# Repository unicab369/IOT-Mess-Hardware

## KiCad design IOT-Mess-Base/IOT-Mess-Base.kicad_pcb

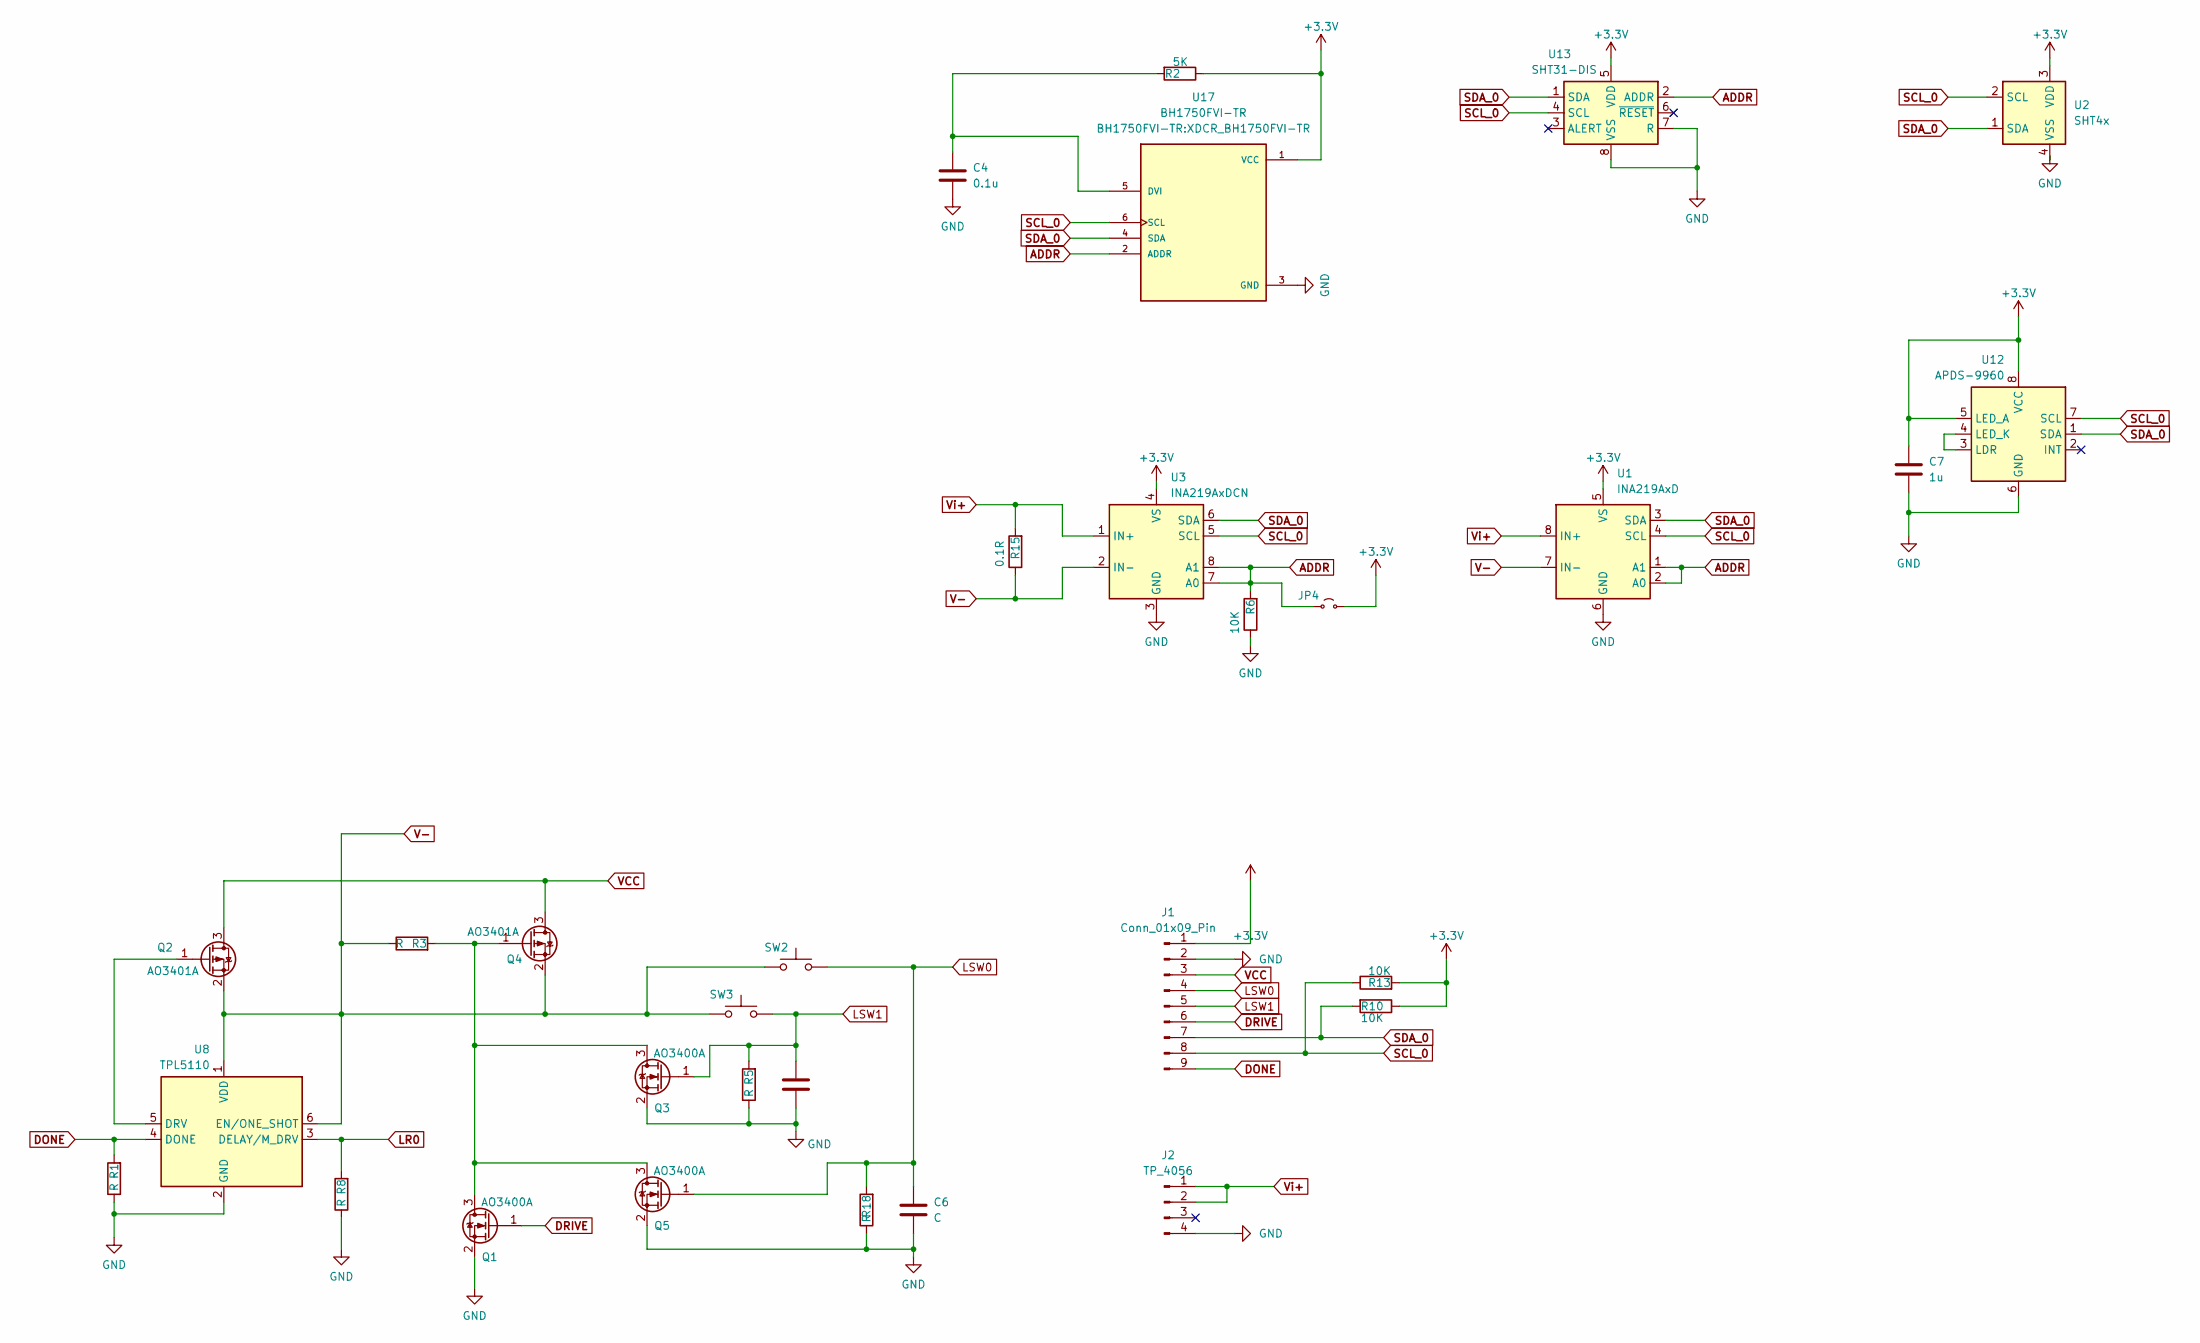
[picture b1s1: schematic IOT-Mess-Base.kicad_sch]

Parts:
C4: 0.1u; C_0603_1608Metric
C5, C6: C; C_0603_1608Metric
C7: 1u; C_0603_1608Metric
J1: Conn_01x09_Pin; PinHeader_1x09_P2.54mm_Vertical
J2: TP_4056; TP_Charger
JP4: Jp_2; SolderJumper-2_P1.3mm_Open_Pad1.0x1.5mm
Q1, Q3, Q5: AO3400A; SOT-23
Q2, Q4: AO3401A; SOT-23
R1, R3, R5, R8, R18: R; R_0603_1608Metric
R2: 5K; R_0603_1608Metric
R6, R10, R13: 10K; R_0603_1608Metric
R15: 0.1R; R_2512_6332Metric
SW2, SW3: SW_Push; SW_SPST_PTS810
U1: INA219AxD; SOIC-8_3.9x4.9mm_P1.27mm
U2: SHT4x; Sensirion_DFN-4_1.5x1.5mm_P0.8mm_SHT4x_NoCentralPad
U3: INA219AxDCN; SOT-23-8
U8: TPL5110; SOT-23-6
U12: APDS-9960; Avago_APDS-9960
U13: SHT31-DIS; Sensirion_DFN-8-1EP_2.5x2.5mm_P0.5mm_EP1.1x1.7mm
U17: BH1750FVI-TR; XDCR_BH1750FVI-TR; PARTREV D

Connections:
+3.3V: C7.1, J1.1, JP4.2 (B), R2.1, R10.1, R13.2, U1.5 (VS), U2.3 (VDD), U3.4 (VS), U12.5 (LED_A), U12.8 (VCC), U13.5 (VDD), U17.1 (VCC)
ADDR: JP4.1 (A), R6.2, U1.1 (A1), U1.2 (A0), U3.7 (A0), U3.8 (A1), U13.2 (ADDR), U17.2 (ADDR)
DONE: J1.9, R1.2, U8.4 (DONE)
DRIVE: J1.6, Q1.1 (G)
GND: C4.2, C5.2, C6.2, C7.2, J1.2, J2.4, Q1.2 (S), Q3.2 (S), Q5.2 (S), R1.1, R5.1, R6.1, R8.1, R18.1, U1.6 (GND), U2.4 (VSS), U3.3 (GND), U8.2 (GND), U12.6 (GND), U13.7 (R), U13.8 (VSS), U13.9 (VSS), U17.3 (GND)
LR0: R8.2, U8.3 (DELAY/M_DRV)
LSW0: C6.1, J1.4, Q5.1 (G), R18.2, SW2.2
LSW1: C5.1, J1.5, Q3.1 (G), R5.2, SW3.2
unnamed: Q1.3 (D), Q3.3 (D), Q4.1 (G), Q5.3 (D), R3.2
unnamed: Q2.1 (G), U8.5 (DRV)
unnamed: U12.3 (LDR), U12.4 (LED_K)
unnamed: C4.1, R2.2, U17.5 (DVI)
SCL_0: J1.8, R13.1, U1.4 (SCL), U2.2 (SCL), U3.5 (SCL), U12.7 (SCL), U13.4 (SCL), U17.6 (SCL)
SDA_0: J1.7, R10.2, U1.3 (SDA), U2.1 (SDA), U3.6 (SDA), U12.1 (SDA), U13.1 (SDA), U17.4 (SDA)
V-: Q2.2 (S), Q4.2 (S), R3.1, R15.1, SW2.1, SW3.1, U1.7 (IN-), U3.2 (IN-), U8.1 (VDD), U8.6 (EN/ONE_SHOT)
VCC: J1.3, Q2.3 (D), Q4.3 (D)
Vi+: J2.1, J2.2, R15.2, U1.8 (IN+), U3.1 (IN+)

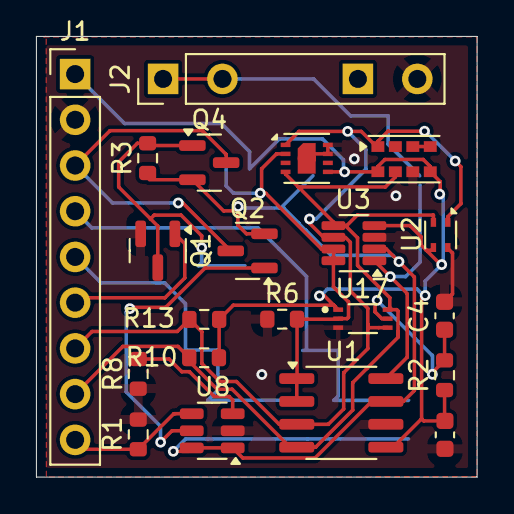
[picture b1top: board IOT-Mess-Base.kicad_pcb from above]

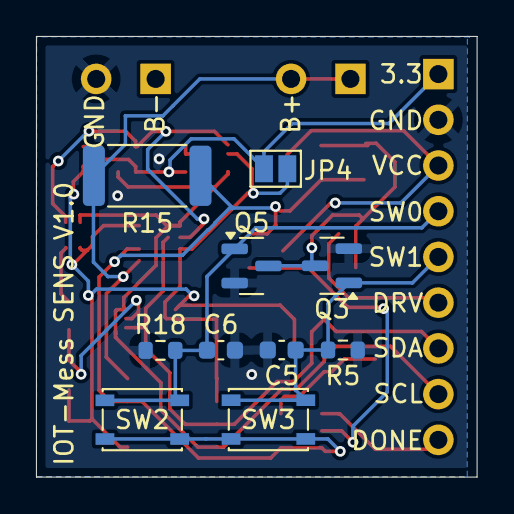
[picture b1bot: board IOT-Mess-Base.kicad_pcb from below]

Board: 2 copper layers, 24.5 x 24.5 mm, 31 parts (10 on the bottom side), 17 nets.

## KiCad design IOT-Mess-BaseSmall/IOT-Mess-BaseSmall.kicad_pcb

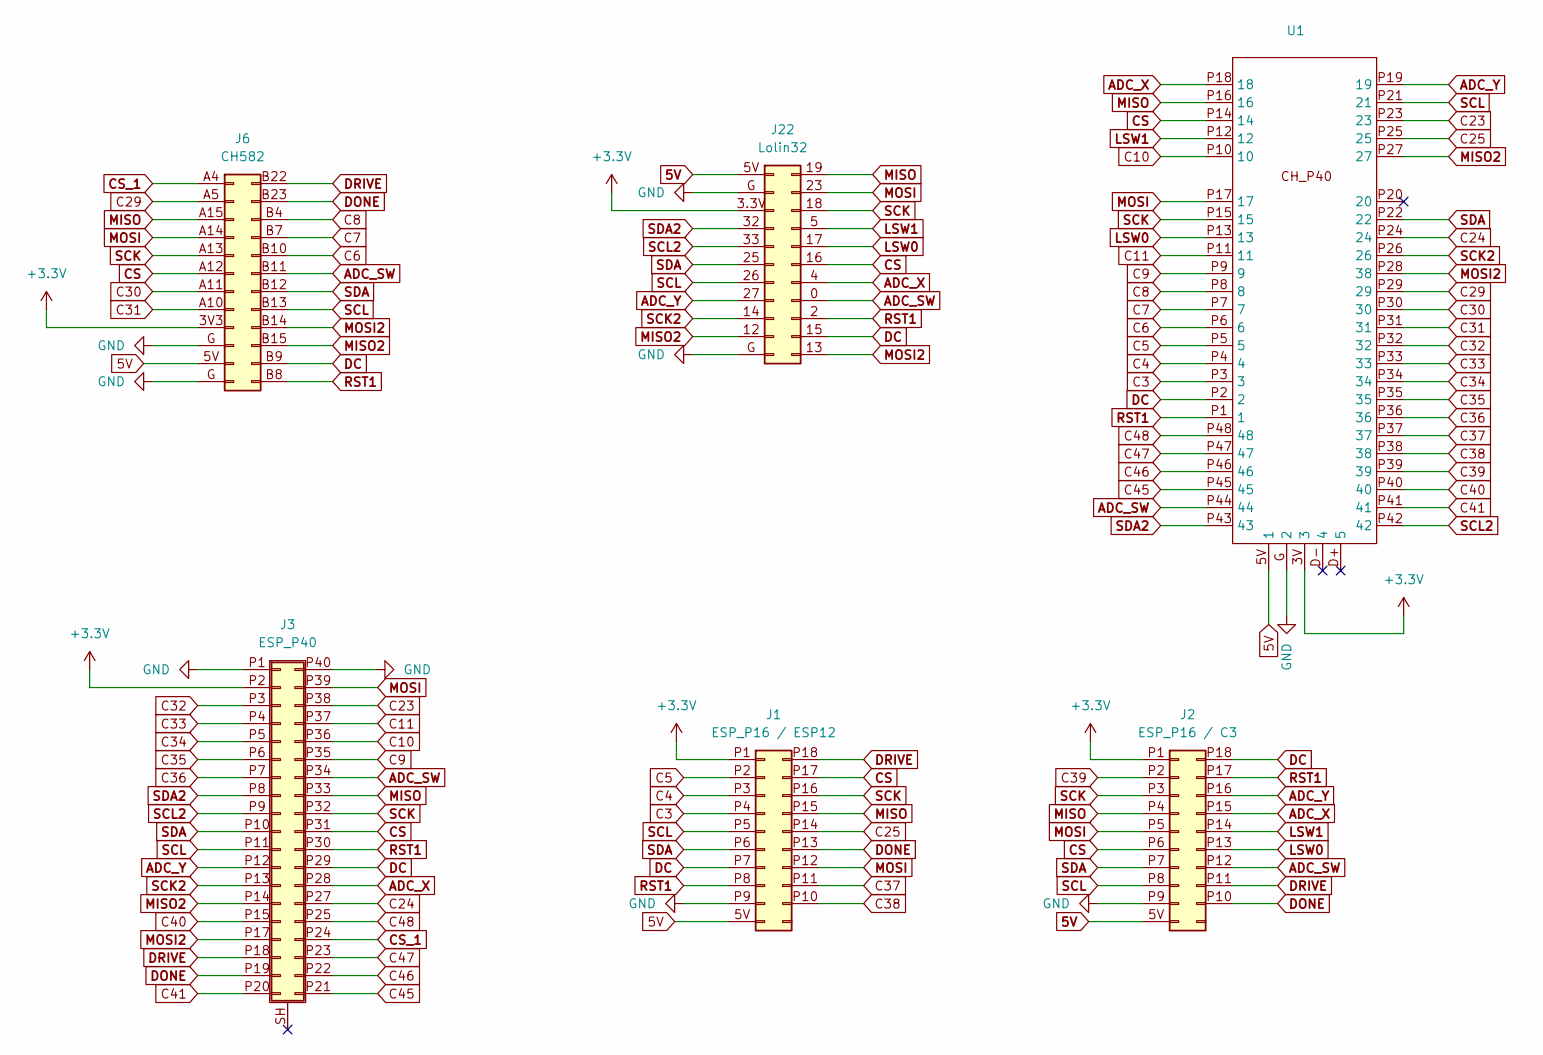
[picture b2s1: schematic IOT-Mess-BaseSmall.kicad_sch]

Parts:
J1: ESP_P16 / ESP12; ESP_P16
J2: ESP_P16 / C3; ESP_P16
J3: ESP_P40
J6: CH582; CH582_Base
J22: Lolin32; Lolin32-Adapter
U1: CH_P48

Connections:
5V: J1.5V (Pin_10), J2.5V (Pin_10), J6.5V (Pin_11), J22.5V (Pin_1), U1.5V (1)
+3.3V: J1.P1 (Pin_1), J2.P1 (Pin_1), J3.P2 (Pin_2), J6.3V3 (Pin_9), J22.3.3V (Pin_3), U1.3V (3)
ADC_SW: J2.P12 (Pin_14), J3.P34 (Pin_26), J6.B11 (Pin_18), J22.0 (Pin_19), U1.P44 (44)
ADC_X: J2.P15 (Pin_17), J3.P28 (Pin_32), J22.4 (Pin_18), U1.P18 (18)
ADC_Y: J2.P16 (Pin_18), J3.P12 (Pin_12), J22.27 (Pin_8), U1.P19 (19)
C3: J1.P4 (Pin_4), U1.P3 (3)
C4: J1.P3 (Pin_3), U1.P4 (4)
C5: J1.P2 (Pin_2), U1.P5 (5)
C6: J6.B10 (Pin_17), U1.P6 (6)
C7: J6.B7 (Pin_16), U1.P7 (7)
C8: J6.B4 (Pin_15), U1.P8 (8)
C9: J3.P35 (Pin_25), U1.P9 (9)
C10: J3.P36 (Pin_24), U1.P10 (10)
C11: J3.P37 (Pin_23), U1.P11 (11)
C23: J3.P38 (Pin_22), U1.P23 (23)
C24: J3.P27 (Pin_33), U1.P24 (24)
C25: J1.P14 (Pin_16), U1.P25 (25)
C29: J6.A5 (Pin_2), U1.P29 (29)
C30: J6.A11 (Pin_7), U1.P30 (30)
C31: J6.A10 (Pin_8), U1.P31 (31)
C32: J3.P3 (Pin_3), U1.P32 (32)
C33: J3.P4 (Pin_4), U1.P33 (33)
C34: J3.P5 (Pin_5), U1.P34 (34)
C35: J3.P6 (Pin_6), U1.P35 (35)
C36: J3.P7 (Pin_7), U1.P36 (36)
C37: J1.P11 (Pin_13), U1.P37 (37)
C38: J1.P10 (Pin_12), U1.P38 (38)
C39: J2.P2 (Pin_2), U1.P39 (39)
C40: J3.P15 (Pin_15), U1.P40 (40)
C41: J3.P20 (Pin_19), U1.P41 (41)
C45: J3.P21 (Pin_38), U1.P45 (45)
C46: J3.P22 (Pin_37), U1.P46 (46)
C47: J3.P23 (Pin_36), U1.P47 (47)
C48: J3.P25 (Pin_34), U1.P48 (48)
CS: J1.P17 (Pin_19), J2.P6 (Pin_6), J3.P31 (Pin_29), J6.A12 (Pin_6), J22.16 (Pin_17), U1.P14 (14)
CS_1: J3.P24 (Pin_35), J6.A4 (Pin_1)
DC: J1.P7 (Pin_7), J2.P18 (Pin_20), J3.P29 (Pin_31), J6.B9 (Pin_23), J22.15 (Pin_21), U1.P2 (2)
DONE: J1.P13 (Pin_15), J2.P10 (Pin_12), J3.P19 (Pin_18), J6.B23 (Pin_14)
DRIVE: J1.P18 (Pin_20), J2.P11 (Pin_13), J3.P18 (Pin_17), J6.B22 (Pin_13)
GND: J1.P9 (Pin_9), J2.P9 (Pin_9), J3.P1 (Pin_1), J3.P40 (Pin_20), J6.G (Pin_10), J22.G (Pin_2), U1.G (2)
LSW0: J2.P13 (Pin_15), J22.17 (Pin_16), U1.P13 (13)
LSW1: J2.P14 (Pin_16), J22.5 (Pin_15), U1.P12 (12)
MISO: J1.P15 (Pin_17), J2.P4 (Pin_4), J3.P33 (Pin_27), J6.A15 (Pin_3), J22.19 (Pin_12), U1.P16 (16)
MISO2: J3.P14 (Pin_14), J6.B15 (Pin_22), J22.12 (Pin_10), U1.P27 (27)
MOSI: J1.P12 (Pin_14), J2.P5 (Pin_5), J3.P39 (Pin_21), J6.A14 (Pin_4), J22.23 (Pin_13), U1.P17 (17)
MOSI2: J3.P17 (Pin_16), J6.B14 (Pin_21), J22.13 (Pin_22), U1.P28 (38)
RST1: J1.P8 (Pin_8), J2.P17 (Pin_19), J3.P30 (Pin_30), J6.B8 (Pin_24), J22.2 (Pin_20), U1.P1 (1)
SCK: J1.P16 (Pin_18), J2.P3 (Pin_3), J3.P32 (Pin_28), J6.A13 (Pin_5), J22.18 (Pin_14), U1.P15 (15)
SCK2: J3.P13 (Pin_13), J22.14 (Pin_9), U1.P26 (26)
SCL: J1.P5 (Pin_5), J2.P8 (Pin_8), J3.P11 (Pin_11), J6.B13 (Pin_20), J22.26 (Pin_7), U1.P21 (21)
SCL2: J3.P9 (Pin_9), J22.33 (Pin_5), U1.P42 (42)
SDA: J1.P6 (Pin_6), J2.P7 (Pin_7), J3.P10 (Pin_10), J6.B12 (Pin_19), J22.25 (Pin_6), U1.P22 (22)
SDA2: J3.P8 (Pin_8), J22.32 (Pin_4), U1.P43 (43)

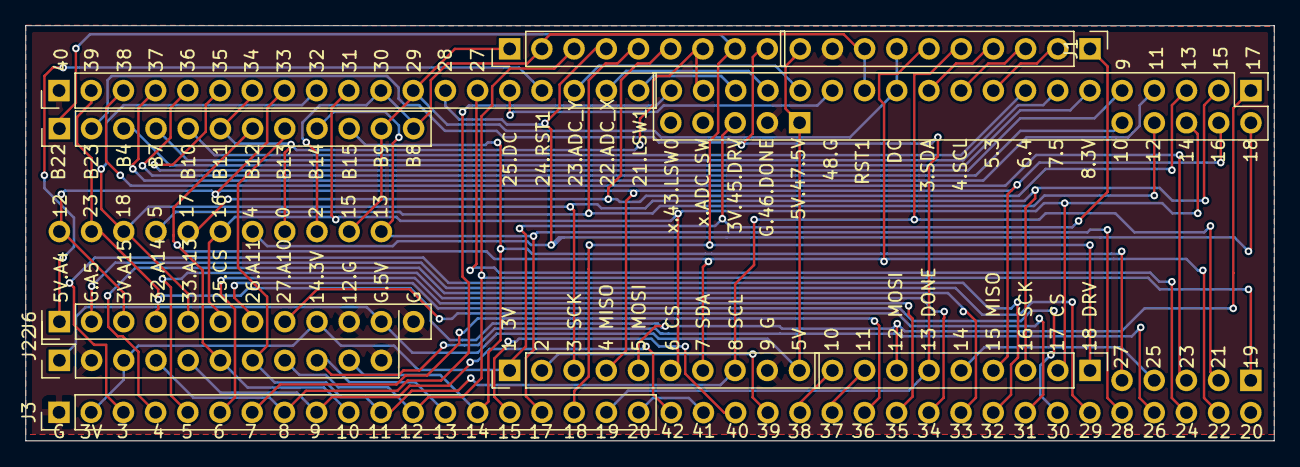
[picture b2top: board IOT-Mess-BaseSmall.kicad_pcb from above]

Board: 2 copper layers, 98.5 x 32.8 mm, 6 parts (0 on the bottom side), 53 nets.

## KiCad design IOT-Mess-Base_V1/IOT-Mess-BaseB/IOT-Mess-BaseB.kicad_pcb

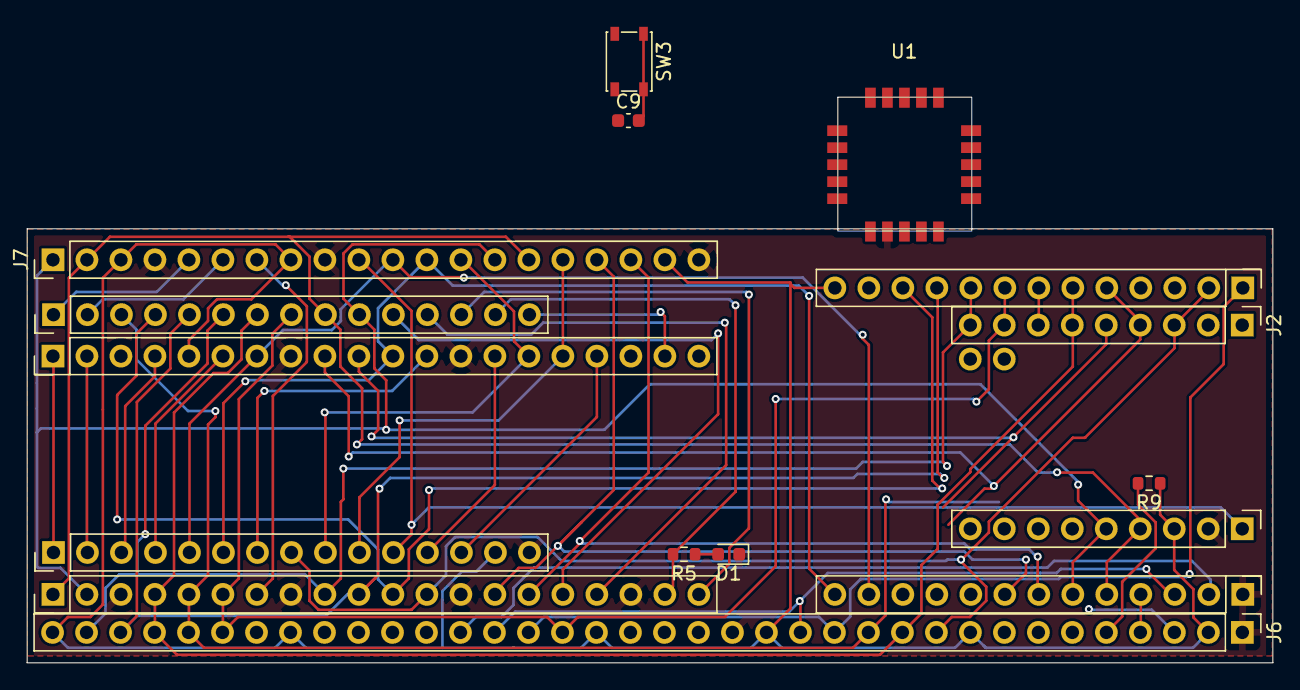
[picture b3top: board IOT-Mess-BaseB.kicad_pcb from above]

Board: 2 copper layers, 93.1 x 42.3 mm, 12 parts (0 on the bottom side), 40 nets.

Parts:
C9: .1u; C_0603_1608Metric
D1: LED; LED_0603_1608Metric
J1: Milk-V Duo
J2: SuperMini_ESP32-H2; SuperMiniH2
J3: CH_P20
J4: Lolin32-Lite
J6: Conn_01x36_Pin; PinHeader_1x36_P2.54mm_Vertical
J7: Conn_01x20_Pin; PinHeader_1x20_P2.54mm_Vertical
R5: 100R; R_0603_1608Metric
R9: 10K; R_0603_1608Metric
SW3: SW_Push; SW_SPST_PTS810
U1: E220-900

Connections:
5V: J2.5V (Pin_18), J3.5V (Pin_11), J7.10
+3.3V: J1.3V (Pin_36), J2.3V (Pin_16), J3.3V (Pin_14), J4.3V (Pin_13a), J6.2, J6.9, J6.15, J6.20, J6.29, J6.36, J7.3, J7.8, J7.19, R9.1, U1.1 (VCC)
ADC_SW: J6.5, R9.2
ADC_X: J1.32, J2.1 (Pin_4), J4.4 (Pin_5a), J6.3
ADC_Y: J1.31, J2.2 (Pin_5), J4.27 (Pin_4b), J6.4
CS_0: J1.6, J2.5 (Pin_8), J3.P13 (Pin_23), J4.5 (Pin_8a), J6.21, J6.31
CS_1: J1.12, J2.0 (Pin_3), J3.P8 (Pin_8), J4.15 (Pin_2a), J6.10
DC: J1.4, J2.3 (Pin_6), J3.P14 (Pin_22), J4.16 (Pin_6a), J6.11, J6.33
DONE: J1.25, J3.P10 (Pin_10), J7.16
DRIVE: J1.26, J3.P9 (Pin_9), J7.13
GND: C9.1, D1.1 (K), J1.G (Pin_3), J2.G (Pin_17), J3.G (Pin_15), J4.G (Pin_1b), J6.1, J6.16, J6.25, J6.30, J7.4, J7.9, J7.20, SW3.2, U1.2 (GND)
L5: J3.P20 (Pin_16), J7.5
L6: J3.P19 (Pin_17), J7.6
L7: J1.7, J7.7
LSW0: J1.34, J3.P5 (Pin_5), J4.36* (Pin_12b), J7.11
LSW1: J1.RUN (Pin_30), J3.P6 (Pin_6), J4.39* (Pin_13b), J7.12
M16: J1.16, J3.RST (Pin_26)
M17: J1.17, J3.XI (Pin_27)
M19: J1.19, J3.D- (Pin_29), R5.2
M20: C9.2, J1.20, J3.XO (Pin_28), SW3.1
M22: J1.22, J3.D+ (Pin_30)
M24: J1.24, J3.CC2 (Pin_13)
M27: J1.27, J3.CC1 (Pin_12)
M29: J1.29, J3.P7 (Pin_7)
M35: J1.35, J3.P4 (Pin_4)
M37: J1.EN (Pin_37), J3.P3 (Pin_3)
M39: J1.VSYS (Pin_39), J3.P2 (Pin_2)
M40: J1.VBUS (Pin_40), J3.P1 (Pin_1)
MISO_0: J1.11, J3.P17 (Pin_19), J4.19 (Pin_11a)
MISO_1: J4.12 (Pin_2b), J6.24
MOSI_0: J1.10, J3.P16 (Pin_20), J4.23 (Pin_10a), J6.34
MOSI_1: J4.13 (Pin_1a), J6.13, J6.22
unnamed: D1.2 (A), R5.1
RST1: J1.5, J2.4 (Pin_7), J3.P18 (Pin_18), J4.17 (Pin_7a), J6.12, J6.32, U1.3 (RST)
SCK_0: J1.9, J2.8 (Pin_9), J3.P15 (Pin_21), J4.18 (Pin_9a), J6.35
SCK_1: J4.14 (Pin_3b), J6.14, J6.23
SCL_0: J1.1, J2.14 (Pin_15), J3.P12 (Pin_24), J4.26 (Pin_5b), J7.2, J7.15
SCL_1: J1.15, J4.33 (Pin_7b), J7.18
SDA_0: J1.2, J2.13 (Pin_14), J3.P11 (Pin_25), J4.25 (Pin_6b), J7.1, J7.14
SDA_1: J1.14, J4.32 (Pin_8b), J7.17

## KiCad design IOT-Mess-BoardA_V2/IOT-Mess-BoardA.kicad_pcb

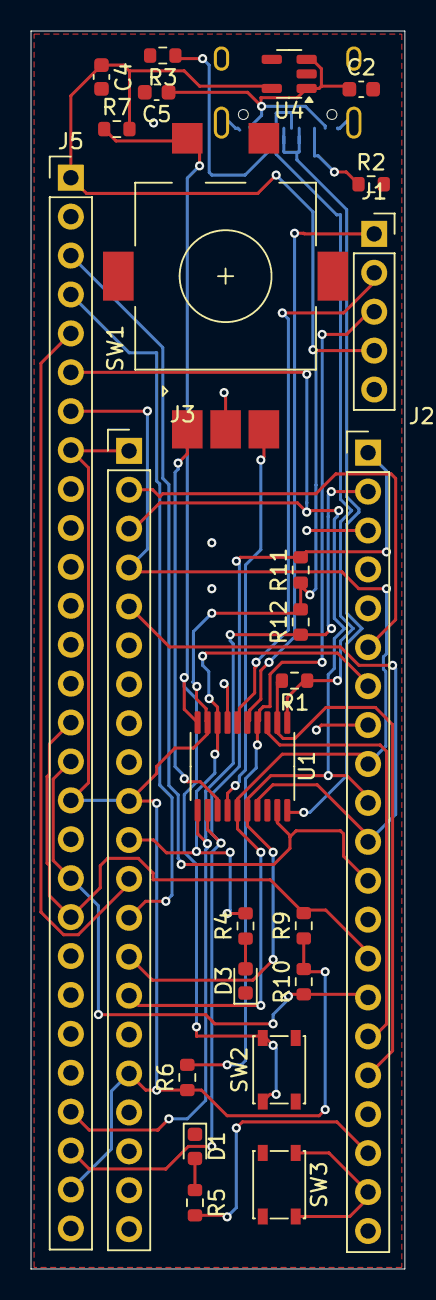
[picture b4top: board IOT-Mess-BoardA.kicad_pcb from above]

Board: 2 copper layers, 24.4 x 80.8 mm, 26 parts (1 on the bottom side), 32 nets.

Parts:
C2: 10u; C_0603_1608Metric
C4, C5: 1u; C_0603_1608Metric
D1, D3: LED; LED_0603_1608Metric
J1: Conn_01x05_Pin; PinSocket_1x05_P2.54mm_Vertical
J2, J3: Conn_01x20_Pin; PinHeader_1x21_P2.54mm_Vertical
J5: Conn_01x28_Pin; PinHeader_1x28_P2.54mm_Vertical
J6: USB_C_Receptacle_USB2.0_16P; USB_C_Receptacle_HRO_TYPE-C-31-M-12
R1: 1.5K; R_0603_1608Metric
R2, R3: 5.1K; R_0603_1608Metric
R4: R; R_0603_1608Metric
R5: 100R; R_0603_1608Metric
R6, R7, R9, R10, R11, R12: 10K; R_0603_1608Metric
SW1: RotaryEncoder_Switch; RotaryEncoder_EC11_SMD
SW2, SW3: SW_Push; SW_SPST_PTS810
U1: CH32V003FxPx; TSSOP-20_4.4x6.5mm_P0.65mm
U4: ME6211C33M5; SOT-23-5

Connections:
ADC_X: J1.1, U1.5 (PA1)
ADC_Y: J1.2, U1.6 (PA2)
CS_0: J2.12, J5.3, U1.19 (PD2)
CS_1: J2.6, J3.2
CS_2: J2.7, J3.11, R4.2, U1.8 (PD0)
D+: J6.A6 (D+), J6.B6 (D+), U1.20 (PD3)
D-: J6.A7 (D-), J6.B7 (D-), R1.1, U1.1 (PD4)
DC: J3.12, J5.5
GND: C2.2, C4.2, C5.2, D1.1 (K), D3.1 (K), J1.5, J2.3, J2.8, J2.13, J2.18, J3.6, J3.16, J5.2, J5.18, J5.28, J6.A1 (GND), J6.A12 (GND), J6.B1 (GND), J6.B12 (GND), J6.S1 (SHIELD), R2.2, R3.2, SW1.C, SW1.S2, SW2.2, SW3.2, U1.7 (VSS), U4.2 (V_{SS})
MISO: J2.11, J3.5, U1.17 (PC7)
MOSI: J2.10, J3.3, J3.14, J5.6, U1.16 (PC6)
unnamed: D1.2 (A), R5.1
unnamed: D3.2 (A), R4.1
unnamed: J2.19, R5.2
unnamed: J2.20, SW3.1
unnamed: J6.A5 (CC1), R3.1
unnamed: J6.B5 (CC2), R2.1
unnamed: C2.1, C5.1, J6.A4 (VBUS), J6.A9 (VBUS), J6.B4 (VBUS), J6.B9 (VBUS), U4.1 (V_{IN}), U4.3 (CE)
RST: J3.13, J5.4
SCK: J2.9, J3.4, J3.15, J5.7, U1.15 (PC5)
SCL_0: J2.1, J5.26, R11.2, U1.12 (PC2)
SCL_3: J2.15, J5.16, J5.19, R10.1
SDA_0: J2.2, J5.25, R12.1, U1.11 (PC1)
SDA_3: J2.14, J5.15, J5.20, R9.2
SW_1: R7.1, SW1.S1, SW2.1, U1.10 (PC0)
SW_2: J1.3, R6.2, U1.4 (PD7)
SW_A: SW1.A, U1.13 (PC3)
SW_B: SW1.B, U1.14 (PC4)
UART0_RX: J2.17, R1.2, U1.2 (PD5)
UART0_TX: J2.16, U1.3 (PD6)
VCC: C4.1, J1.4, J3.1, J3.10, J3.17, J5.1, J5.8, J5.17, J5.27, R6.1, R7.2, R9.1, R10.2, R11.1, R12.2, U1.9 (VDD), U4.5 (V_{OUT})
X: J5.21, J5.22, J5.23, J5.24

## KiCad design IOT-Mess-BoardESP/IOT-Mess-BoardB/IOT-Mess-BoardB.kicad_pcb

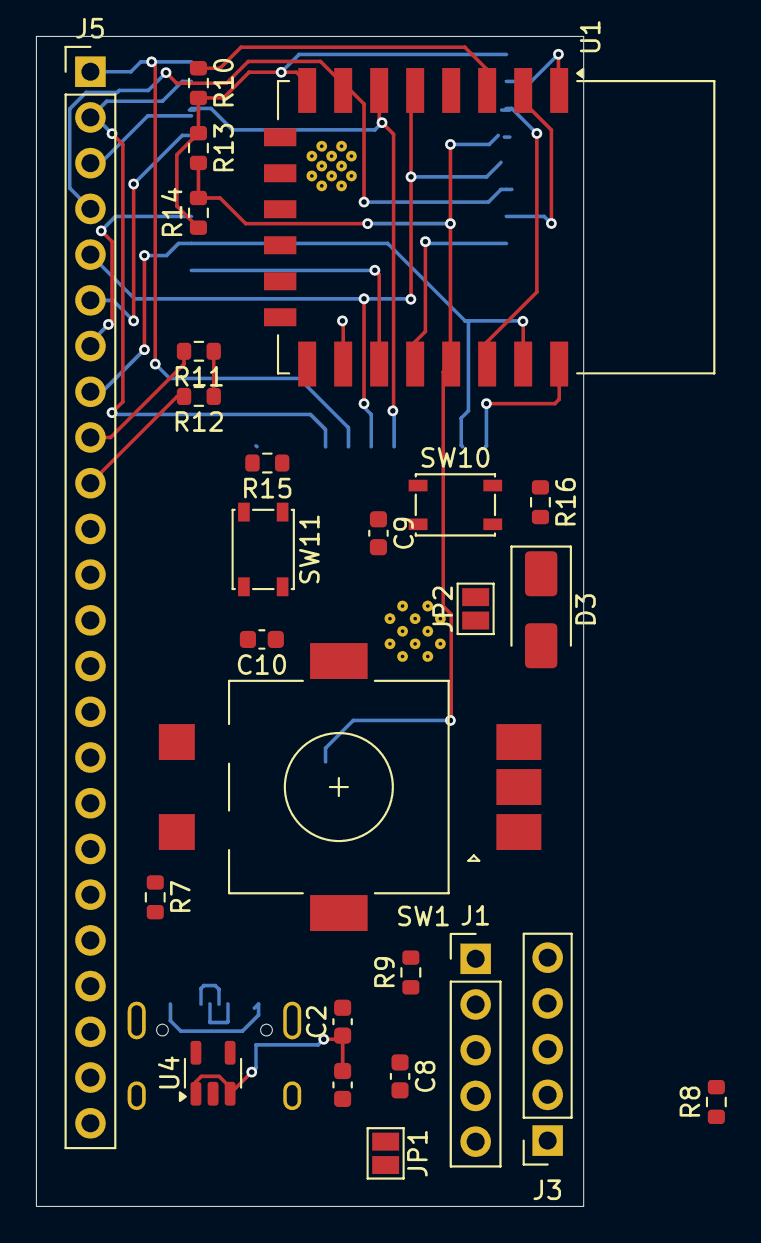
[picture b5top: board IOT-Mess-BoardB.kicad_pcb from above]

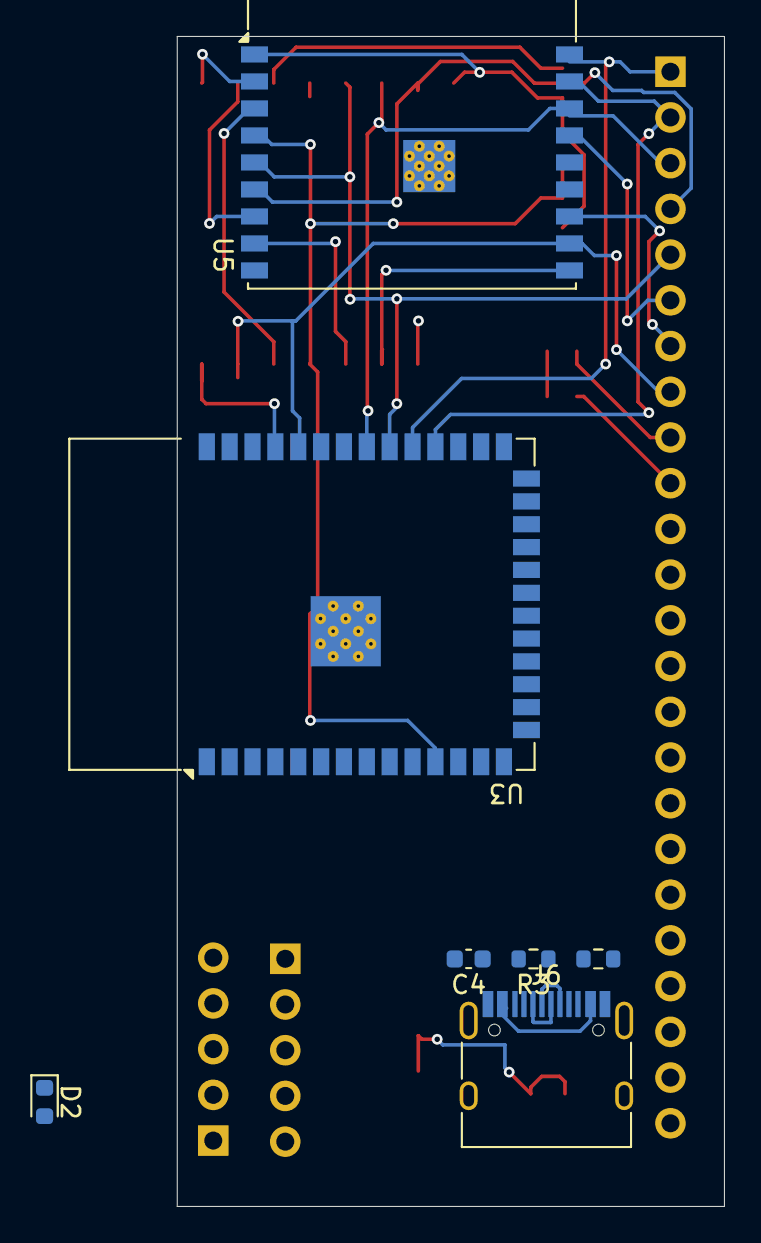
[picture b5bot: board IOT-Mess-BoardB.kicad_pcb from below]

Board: 2 copper layers, 30.4 x 65.0 mm, 33 parts (7 on the bottom side), 39 nets.

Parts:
C2: 10u; C_0603_1608Metric
C4, C5: 1u; C_0603_1608Metric
C8, C9, C10: .1u; C_0603_1608Metric
D2: LED; LED_0603_1608Metric
D3: SS14; D_SMA
J1: Conn_01x05_Pin; PinHeader_1x05_P2.54mm_Vertical
J3: Conn_01x05_Pin; PinSocket_1x05_P2.54mm_Vertical
J5: Conn_01x24_Pin; PinHeader_1x24_P2.54mm_Vertical
J6: USB_C_Receptacle_USB2.0_16P; USB_C_Receptacle_HRO_TYPE-C-31-M-12
JP1, JP2: Jumper_2; SolderJumper-2_P1.3mm_Open_Pad1.0x1.5mm
R2, R3: 5.1K; R_0603_1608Metric
R7, R9, R10, R11, R12, R13, R14, R15, R16: 10K; R_0603_1608Metric
R8: 100R; R_0603_1608Metric
SW1: RotaryEncoder; RotaryEncoder_EC11_SMD
SW10, SW11: SW_Push; SW_SPST_PTS810
U1: ESP-12F; ESP-12E
U3: ESP32-S3-WROOM-1
U4: ME6211C33M5; SOT-23-5
U5: ESP32-C3-WROOM-02

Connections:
5V: C2.1, C5.1, D3.1 (K), JP2.2 (B), U4.1 (V_{IN}), U4.3 (CE)
+3.3V: C4.1, J3.4, J5.23, R7.2, R9.1, R10.2, R11.1, R12.1, R13.1, R14.1, R15.2, R16.2, U1.8 (VCC), U3.2 (3V3), U4.5 (V_{OUT}), U5.1 (3V3)
ADC_X: J3.1, J5.19, U3.6 (IO6)
ADC_Y: J3.2, J5.20, U3.7 (IO7)
BOOT: C9.1, R16.1, SW10.1, U1.18 (GPIO0), U3.27 (IO0), U5.8 (GPIO9)
CS_0: J5.6, U1.16 (GPIO15), U3.29 (IO36), U5.15 (GPIO3/ADC1_CH3)
CS_1: J5.16, U3.35 (IO42)
D+: J6.A6 (D+), J6.B6 (D+), U3.14 (USB_D+), U5.14 (GPIO19/USB_D+)
D-: J6.A7 (D-), J6.B7 (D-), U3.13 (USB_D-), U5.13 (GPIO18/USB_D-)
DC: J5.1, U3.31 (IO38), U5.18 (GPIO0/ADC1_CH0/XTAL_32K_P)
GND: C2.2, C4.2, C5.2, C8.1, C9.2, C10.2, D2.1 (K), J3.5, J5.24, J6.A1 (GND), J6.A12 (GND), J6.B1 (GND), J6.B12 (GND), J6.S1 (SHIELD), R2.2, R3.2, SW1.C, SW1.S2, SW10.2, SW11.2, U1.15 (GND), U3.1 (GND), U3.40 (GND), U3.41 (GND), U4.2 (V_{SS}), U5.9 (GND), U5.19 (GND)
LED22: R8.2, U3.38 (IO2)
unnamed: D2.2 (A), R8.1
unnamed: D3.2 (A), JP1.2 (B), JP2.1 (A)
unnamed: J6.A5 (CC1), R3.1
unnamed: J6.B5 (CC2), R2.1
unnamed: J6.A4 (VBUS), J6.A9 (VBUS), J6.B4 (VBUS), J6.B9 (VBUS), JP1.1 (A)
unnamed: R10.1, U1.3 (EN)
RST_SW: C10.1, R15.1, SW11.1, U1.1 (~RST), U3.3 (EN), U5.2 (EN/CHIP_PU)
SCL_0: J5.22, R13.2, R14.2, U1.19 (GPIO4), U3.11 (IO18), U5.4 (GPIO5/ADC2_CH0)
SCL_3: J5.10, R12.2, U3.9 (IO16)
SDA_0: J5.21, U1.20 (GPIO5), U3.10 (IO17), U5.3 (GPIO4/ADC1_CH4)
SDA_3: J5.9, R11.2, U3.8 (IO15)
SPIA_MISO: J5.3, U1.6 (GPIO12), U3.33 (IO40), U5.16 (GPIO2/ADC1_CH2)
SPIA_MOSI: J5.4, U1.7 (GPIO13), U3.39 (IO1), U5.6 (GPIO7)
SPIA_SCK: J5.5, U1.5 (GPIO14), U3.32 (IO39), U5.5 (GPIO6)
SPIB_MISO: J5.15, U3.25 (IO48)
SPIB_MOSI: J5.14, U3.24 (IO47)
SPIB_SCK: J5.13, U3.17 (IO9)
SPI_RST: J5.2, U3.30 (IO37), U5.17 (GPIO1/ADC1_CH1/XTAL_32K_N)
SW_A: J5.17, SW1.A, U1.2 (ADC), U3.4 (IO4), U5.7 (GPIO8)
SW_B: J5.18, SW1.B, U1.17 (GPIO2), U3.5 (IO5), U5.10 (GPIO10)
SW_C: C8.2, J5.12, R7.1, SW1.S1, U3.12 (IO8)
SW_D: J3.3, J5.11, R9.2, U3.21 (IO13)
UART0_RX: J5.8, U1.21 (GPIO3/RXD), U3.36 (RXD0), U5.11 (GPIO20/U0RXD)
UART0_TX: J5.7, U1.22 (GPIO1/TXD), U3.37 (TXD0), U5.12 (GPIO21/U0TXD)
UART1_RX: J1.4, U3.19 (IO11)
UART1_TX: J1.5, U3.18 (IO10)
WLED: J1.3, U1.4 (GPIO16), U3.28 (IO35)

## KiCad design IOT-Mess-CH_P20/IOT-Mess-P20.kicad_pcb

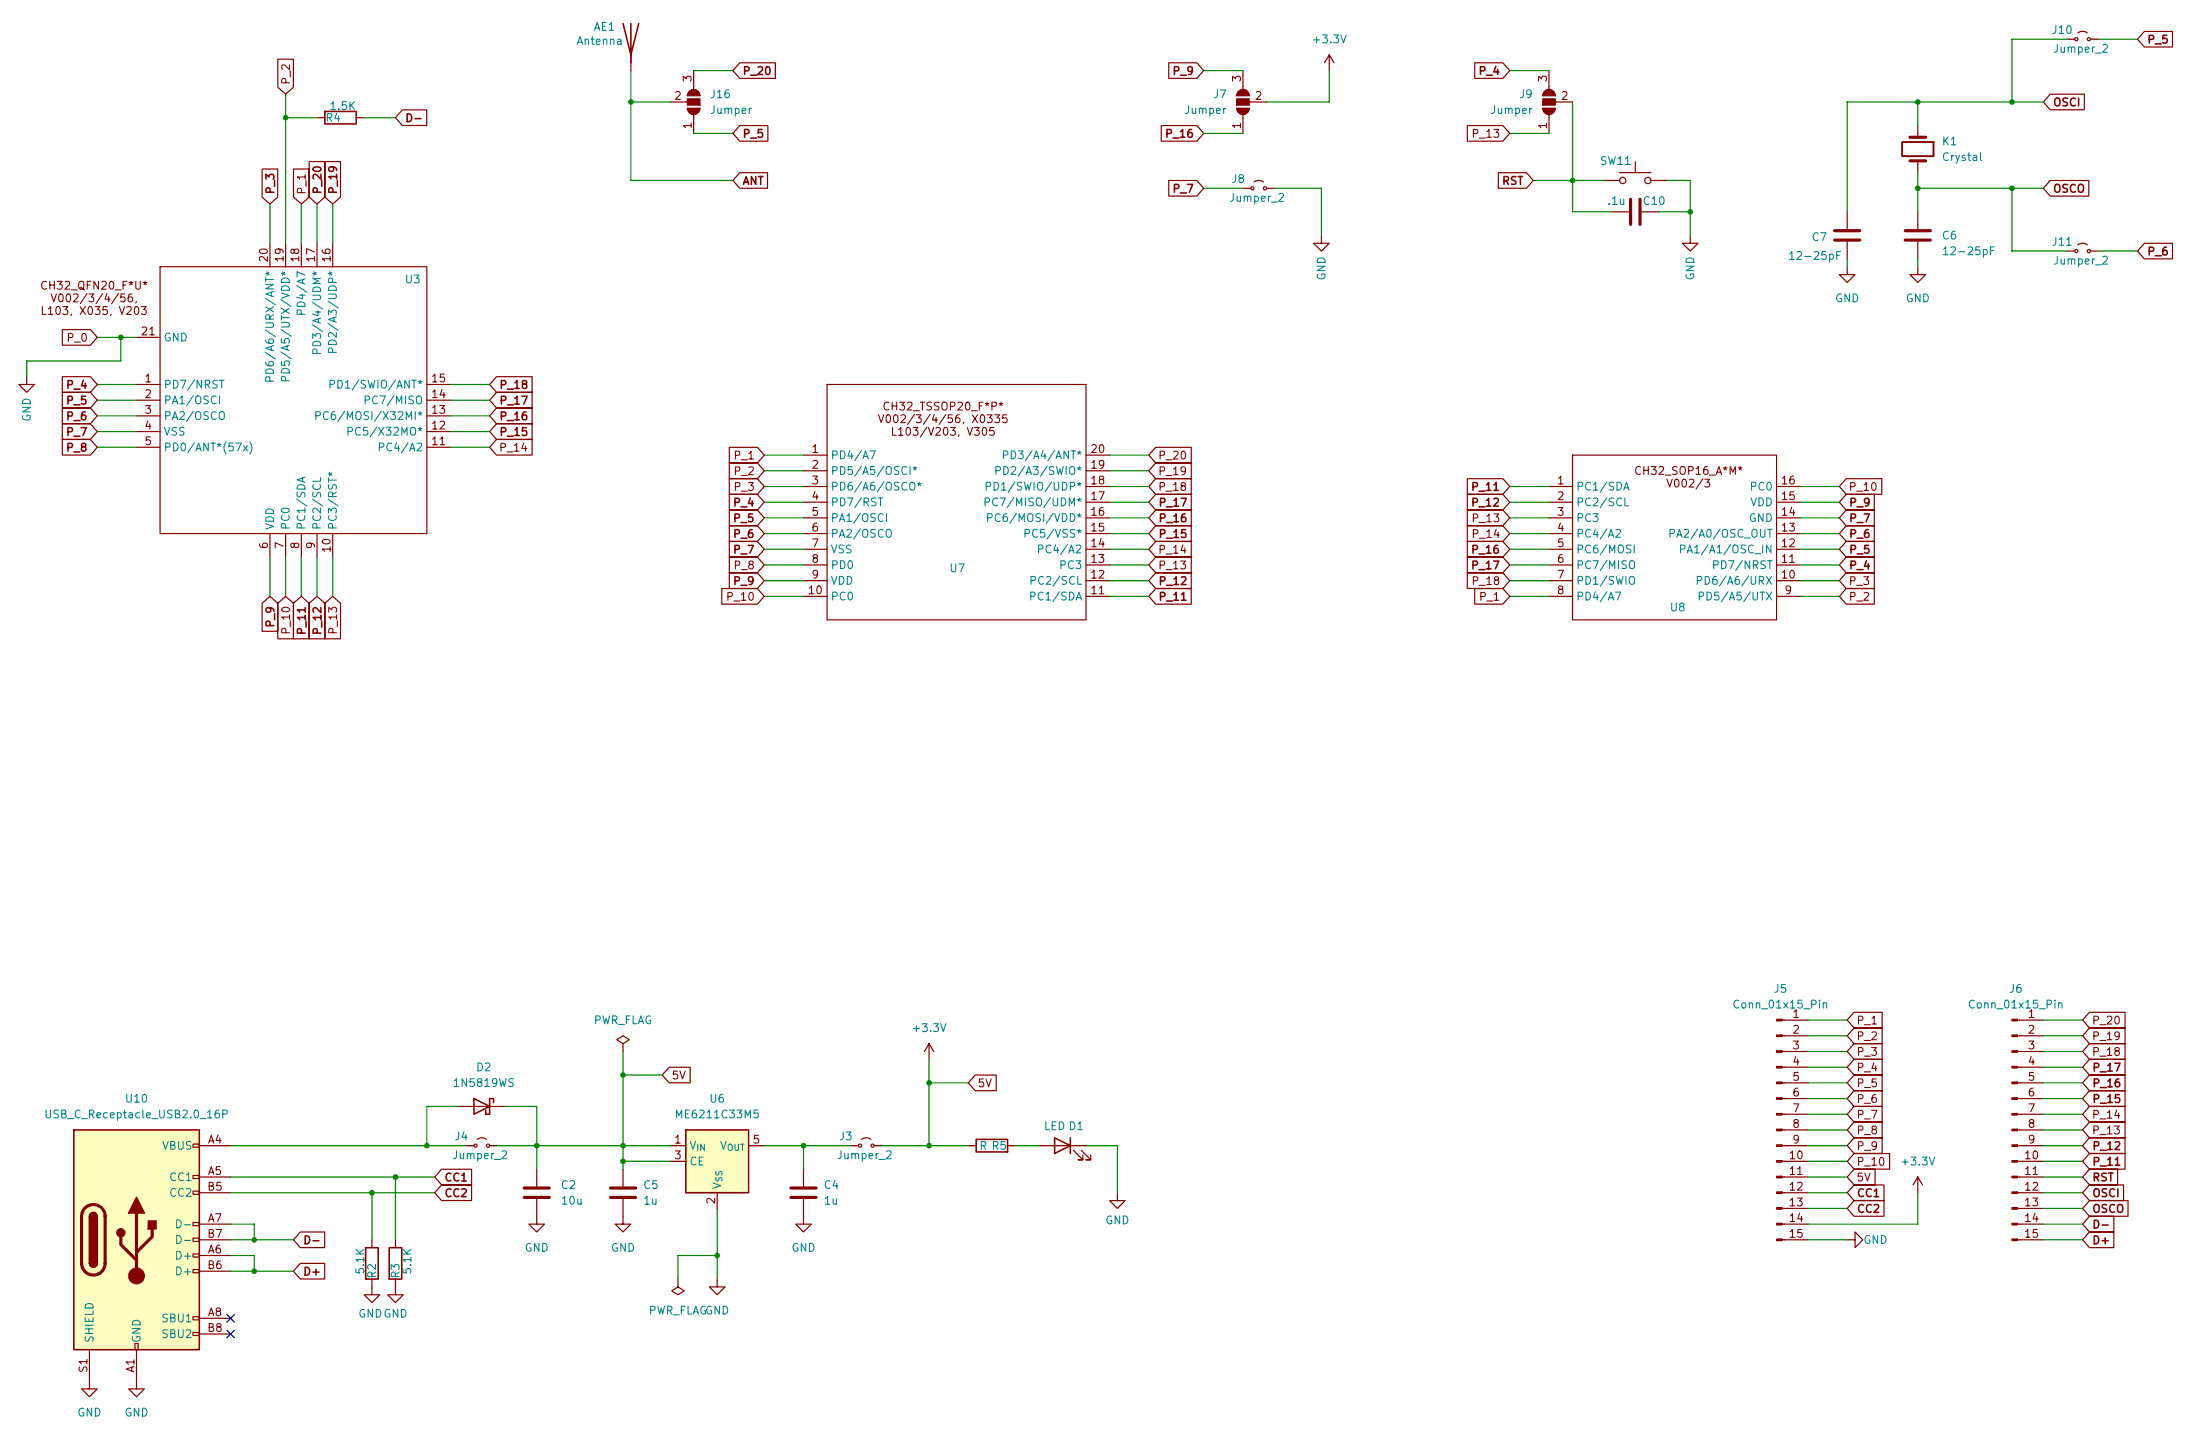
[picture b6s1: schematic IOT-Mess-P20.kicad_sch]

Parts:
AE1: Antenna; Texas_SWRA117D_2.4GHz_Right
C2: 10u; C_0603_1608Metric
C4, C5: 1u; C_0603_1608Metric
C6, C7: 12-25pF; C_0603_1608Metric
C10: .1u; C_0603_1608Metric
D1: LED; LED_0603_1608Metric
D2: 1N5819WS; D_SOD-323
J3, J4, J8, J10, J11: Jumper_2; Jumpper-triangle
J5, J6: Conn_01x15_Pin; PinHeader_1x15_P2.54mm_Vertical
J7, J9, J16: Jumper; Jumper-3_P1.3mm_Open_RoundedPad1.0x1.5mm
K1: Crystal; Crystal_SMD_3225-4Pin_3.2x2.5mm
R2, R3: 5.1K; R_0603_1608Metric
R4: 1.5K; R_0603_1608Metric
R5: R; R_0603_1608Metric
SW11: SW_Push; SW_SPST_PTS810
U3: QFN-20-1EP_3x3mm_P0.4mm_EP1.65x1.65mm_ThermalVias
U6: ME6211C33M5; SOT-23-5
U7: TSSOP-20_4.4x6.5mm_P0.65mm
U8: SOP-16_3.9x9.9mm_P1.27mm
U10: USB_C_Receptacle_USB2.0_16P; USB_C_Receptacle_HRO_TYPE-C-31-M-12

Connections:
5V: C2.1, C5.1, D2.1 (K), J3.2 (B), J4.2 (B), J5.11, J5.14, J7.2 (C), R5.1, U6.1 (V_{IN}), U6.3 (CE)
ANT: AE1.1 (A), J16.2 (C)
CC1: J5.12, R3.1, U10.A5 (CC1)
CC2: J5.13, R2.1, U10.B5 (CC2)
D+: J6.15, U10.A6 (D+), U10.B6 (D+)
D-: J6.14, R4.1, U10.A7 (D-), U10.B7 (D-)
unnamed: D1.2 (A), R5.2
unnamed: D2.2 (A), J4.1 (A), U10.A4 (VBUS), U10.A9 (VBUS), U10.B4 (VBUS), U10.B9 (VBUS)
unnamed: C4.1, J3.1 (A), U6.5 (V_{OUT})
OSCI: C7.1, J6.12, J10.1 (A), K1.1
OSCO: C6.1, J6.13, J11.1 (A), K1.2
P_0: C2.2, C4.2, C5.2, C6.2, C7.2, C10.2, D1.1 (K), J5.15, J8.2 (B), R2.2, R3.2, SW11.2, U3.21 (GND), U6.2 (V_{SS}), U10.A1 (GND), U10.A12 (GND), U10.B1 (GND), U10.B12 (GND), U10.S1 (SHIELD)
P_1: J5.1, U3.18 (PD4/A7), U7.1 (PD4/A7), U8.8 (PD4/A7)
P_2: J5.2, R4.2, U3.19 (PD5/A5/UTX/VDD*), U7.2 (PD5/A5/OSCI*), U8.9 (PD5/A5/UTX)
P_3: J5.3, U3.20 (PD6/A6/URX/ANT*), U7.3 (PD6/A6/OSCO*), U8.10 (PD6/A6/URX)
P_4: J5.4, J9.3 (B), U3.1 (PD7/NRST), U7.4 (PD7/RST), U8.11 (PD7/NRST)
P_5: J5.5, J10.2 (B), J16.1 (A), U3.2 (PA1/OSCI), U7.5 (PA1/OSCI), U8.12 (PA1/A1/OSC_IN)
P_6: J5.6, J11.2 (B), U3.3 (PA2/OSCO), U7.6 (PA2/OSCO), U8.13 (PA2/A0/OSC_OUT)
P_7: J5.7, J8.1 (A), U3.4 (VSS), U7.7 (VSS), U8.14 (GND)
P_8: J5.8, U3.5 (PD0/ANT*(57x)), U7.8 (PD0)
P_9: J5.9, J7.3 (B), U3.6 (VDD), U7.9 (VDD), U8.15 (VDD)
P_10: J5.10, U3.7 (PC0), U7.10 (PC0), U8.16 (PC0)
P_11: J6.10, U3.8 (PC1/SDA), U7.11 (PC1/SDA), U8.1 (PC1/SDA)
P_12: J6.9, U3.9 (PC2/SCL), U7.12 (PC2/SCL), U8.2 (PC2/SCL)
P_13: J6.8, J9.1 (A), U3.10 (PC3/RST*), U7.13 (PC3), U8.3 (PC3)
P_14: J6.7, U3.11 (PC4/A2), U7.14 (PC4/A2), U8.4 (PC4/A2)
P_15: J6.6, U3.12 (PC5/X32MO*), U7.15 (PC5/VSS*)
P_16: J6.5, J7.1 (A), U3.13 (PC6/MOSI/X32MI*), U7.16 (PC6/MOSI/VDD*), U8.5 (PC6/MOSI)
P_17: J6.4, U3.14 (PC7/MISO), U7.17 (PC7/MISO/UDM*), U8.6 (PC7/MISO)
P_18: J6.3, U3.15 (PD1/SWIO/ANT*), U7.18 (PD1/SWIO/UDP*), U8.7 (PD1/SWIO)
P_19: J6.2, U3.16 (PD2/A3/UDP*), U7.19 (PD2/A3/SWIO*)
P_20: J6.1, J16.3 (B), U3.17 (PD3/A4/UDM*), U7.20 (PD3/A4/ANT*)
RST: C10.1, J6.11, J9.2 (C), SW11.1

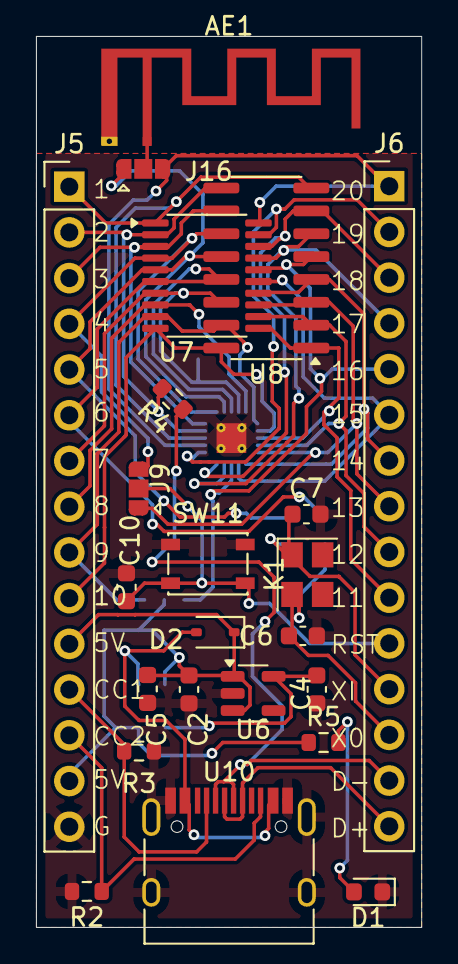
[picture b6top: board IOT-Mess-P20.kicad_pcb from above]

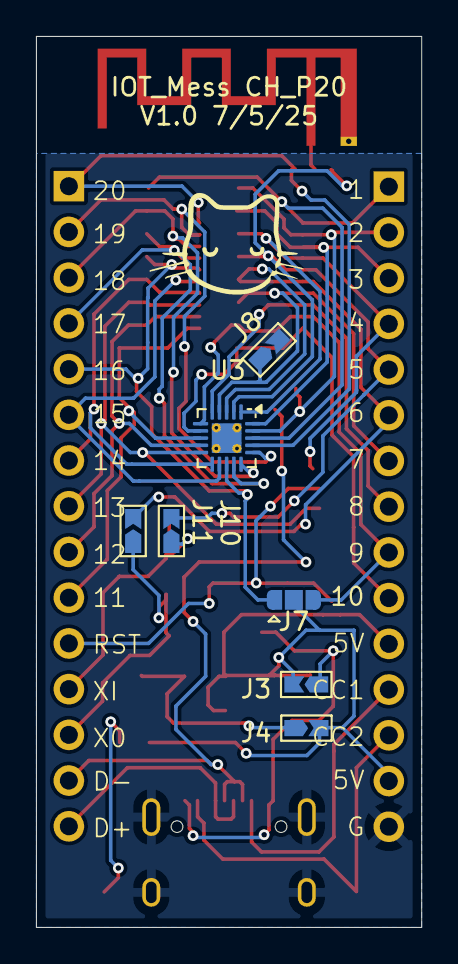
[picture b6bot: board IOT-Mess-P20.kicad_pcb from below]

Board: 2 copper layers, 21.4 x 49.5 mm, 30 parts (7 on the bottom side), 33 nets.
